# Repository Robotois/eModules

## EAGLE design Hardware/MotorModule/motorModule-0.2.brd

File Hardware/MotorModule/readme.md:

# Motor Module

The motor module is powered by the MCU [ATMEGA328](http://www.atmel.com/devices/atmega328.aspx), as you can see this is the same MCU used in the Arduino [UNO](https://www.arduino.cc/en/Main/ArduinoBoardUno). The firmware of this MCU was coded to control two motors using PWM signals. Until the last version of this module, the firmware for the ATMEGA328 is coded in C language (AVR).

This module has the following features:

* An open firmware for the ATMEGA328, this means that you can modify the code or even use Arduino sketches. The module has an SPI interface for programming the MCU.

* This module is ready for controlling motors without feedback, this means that we can control the direction of rotation, and control the speed by PWM signals.

* Also, the motor module has the necessary components to implement speed and direction control using quadrature encoder sensors. The quadrature sensors provide a reliable feedback for controlling the speed of the motor and therefore we can control the speed of the wheels of a robot.

* There are two lines of the RJ25 connector that provide the voltage for the motors, the advantage of this configuration is that we will have a better current flow trough the cables. The voltage to power up the motors is taken directly from the batteries. The typical voltages of a LiPo battery are: 7.4V for a two cell in series (2S) configuration and 11.1V for 3 cells in series (3S).

* The driver for the motors consists of the IC [TB6612FNG](https://www.sparkfun.com/products/9457), this IC was chosen because it is basically a Mosfet H-bridge and it is efficient enough for small robot applications.

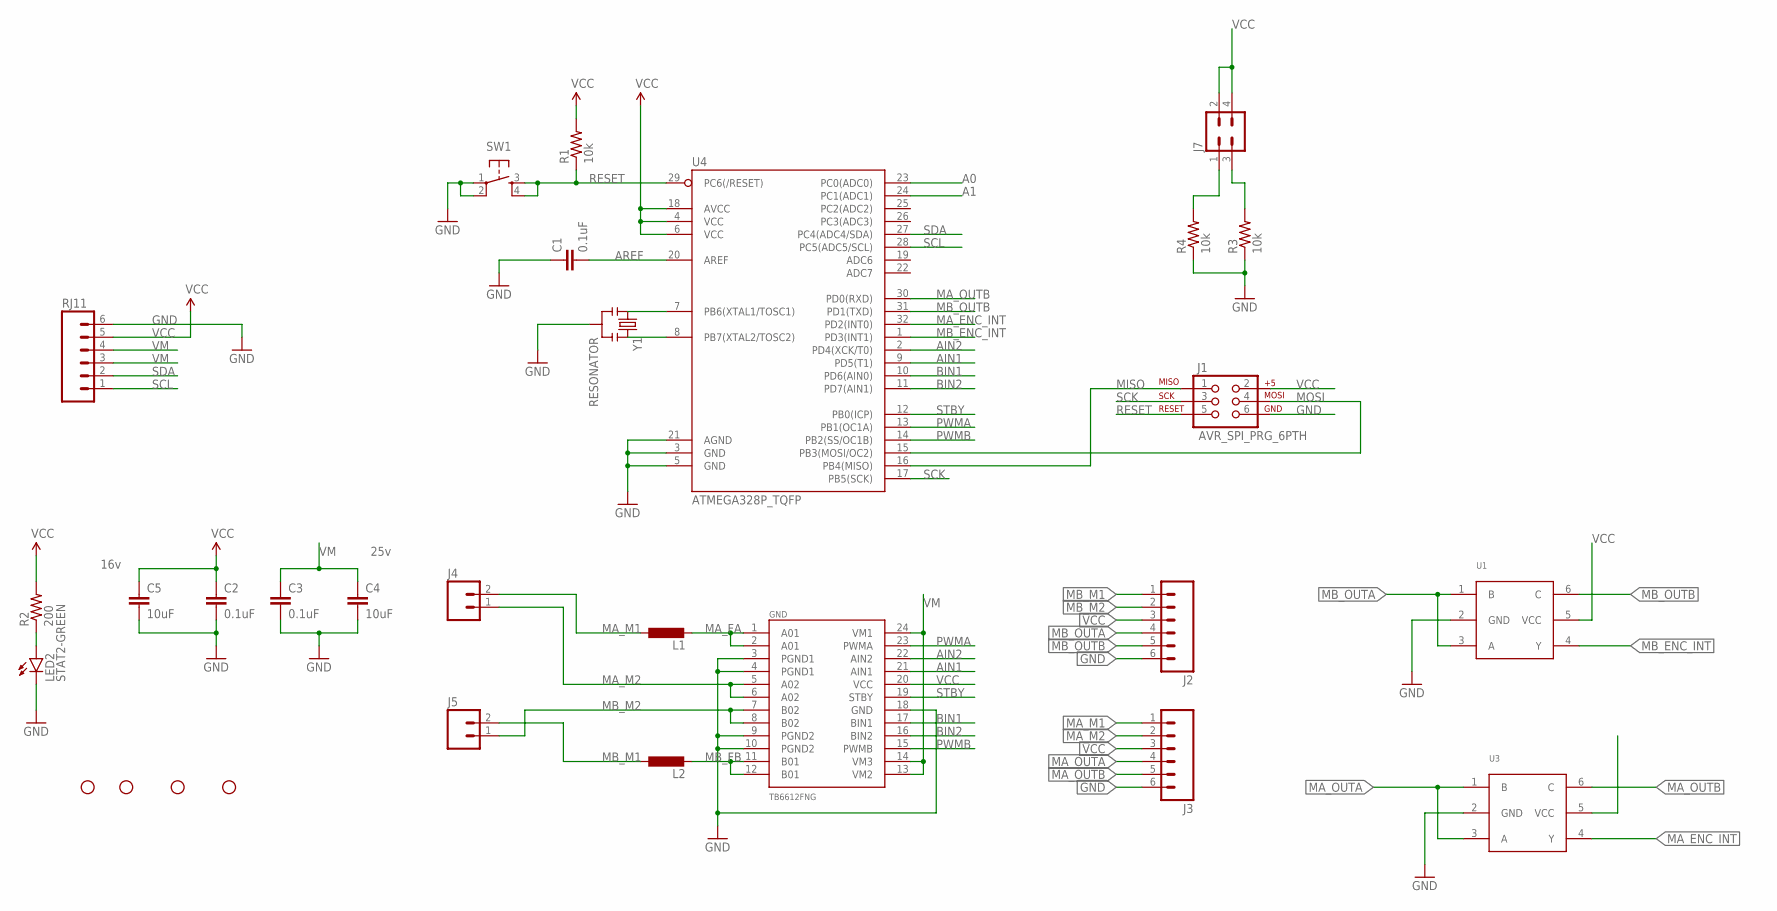
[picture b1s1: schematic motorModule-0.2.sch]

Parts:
C1, C2, C3: 0.1uF; 0603-CAP
C4, C5: 10uF; 0805
GND: TB6612FNG; SSOP24
H1, H2, H3, H4: STAND-OFFPLATED; STAND-OFF-PLATED
J1: AVR_SPI_PRG_6PTH; 2X3
J2, J3: M06JST-PH-6TH; JST-PH-6-TH
J4, J5: M02JST-PTH-VERT; JST-2-PTH-VERT
J7: M02X2; 2X2
L1, L2: L-EUL1812; L1812
LED2: STAT2-GREEN; LED-0603
R1, R3, R4: 10k; 0603-RES
R2: 200; 0603-RES
RJ11: M06RJ11; RJ11-6P6C
SW1: SWITCH_SPST_4_PINKMR2; TACTILE_SWITCH_SMD-3
U1, U3: 74LVC1G58; SOT363
U4: ATMEGA328P_TQFP; TQFP32-08
Y1: RESONATOR; RESONATOR-MURATA

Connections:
A0: J7.3, R3.2, U4.23 (PC0(ADC0))
A1: J7.1, R4.2, U4.24 (PC1(ADC1))
AIN1: GND.21 (AIN1), U4.9 (PD5(T1))
AIN2: GND.22 (AIN2), U4.2 (PD4(XCK/T0))
AREF: C1.2, U4.20 (AREF)
BIN1: GND.17 (BIN1), U4.10 (PD6(AIN0))
BIN2: GND.16 (BIN2), U4.11 (PD7(AIN1))
GND: C1.1, C2.2, C3.2, C4.2, C5.2, GND.3 (PGND1), GND.4 (PGND1), GND.9 (PGND2), GND.10 (PGND2), GND.18 (GND), J1.6, J2.6, J3.6, LED2.C, R3.1, R4.1, RJ11.6, SW1.1, SW1.2, U1.2 (GND), U3.2 (GND), U4.3 (GND), U4.5 (GND), U4.21 (AGND), Y1.2
MA_ENC_INT: U3.4 (Y), U4.32 (PD2(INT0))
MA_FA: GND.1 (A01), GND.2 (A01), L1.2
MA_M1: J3.1, J4.2, L1.1
MA_M2: GND.5 (A02), GND.6 (A02), J3.2, J4.1
MA_OUTA: J3.4, U3.1 (B), U3.3 (A)
MA_OUTB: J3.5, U3.6 (C), U4.30 (PD0(RXD))
MB_ENC_INT: U1.4 (Y), U4.1 (PD3(INT1))
MB_FB: GND.11 (B01), GND.12 (B01), L2.2
MB_M1: J2.1, J5.2, L2.1
MB_M2: GND.7 (B02), GND.8 (B02), J2.2, J5.1
MB_OUTA: J2.4, U1.1 (B), U1.3 (A)
MB_OUTB: J2.5, U1.6 (C), U4.31 (PD1(TXD))
MISO: J1.1, U4.16 (PB4(MISO))
MOSI: J1.4, U4.15 (PB3(MOSI/OC2))
unnamed: U4.7 (PB6(XTAL1/TOSC1)), Y1.1
unnamed: U4.8 (PB7(XTAL2/TOSC2)), Y1.3
unnamed: LED2.A, R2.1
PWMA: GND.23 (PWMA), U4.13 (PB1(OC1A))
PWMB: GND.15 (PWMB), U4.14 (PB2(SS/OC1B))
RESET: J1.5, R1.1, SW1.3, SW1.4, U4.29 (PC6(/RESET))
SCK: J1.3, U4.17 (PB5(SCK))
SCL: RJ11.1, U4.28 (PC5(ADC5/SCL))
SDA: RJ11.2, U4.27 (PC4(ADC4/SDA))
STBY: GND.19 (STBY), U4.12 (PB0(ICP))
VCC: C2.1, C5.1, GND.20 (VCC), J1.2, J2.3, J3.3, J7.2, J7.4, R1.2, R2.2, RJ11.5, U1.5 (VCC), U3.5 (VCC), U4.4 (VCC), U4.6 (VCC), U4.18 (AVCC)
VM: C3.1, C4.1, GND.13 (VM2), GND.14 (VM3), GND.24 (VM1), RJ11.3, RJ11.4

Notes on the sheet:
16v
25v

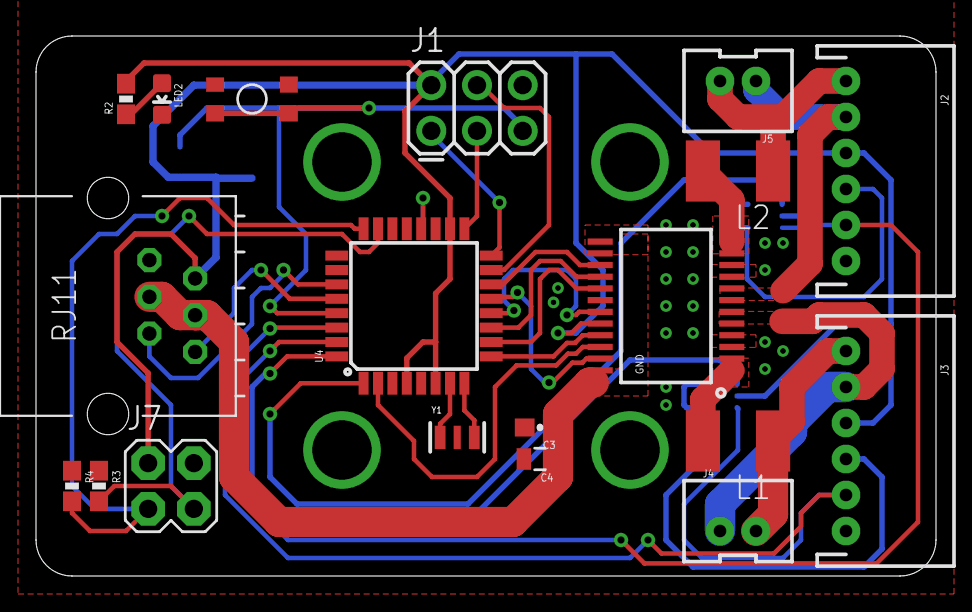
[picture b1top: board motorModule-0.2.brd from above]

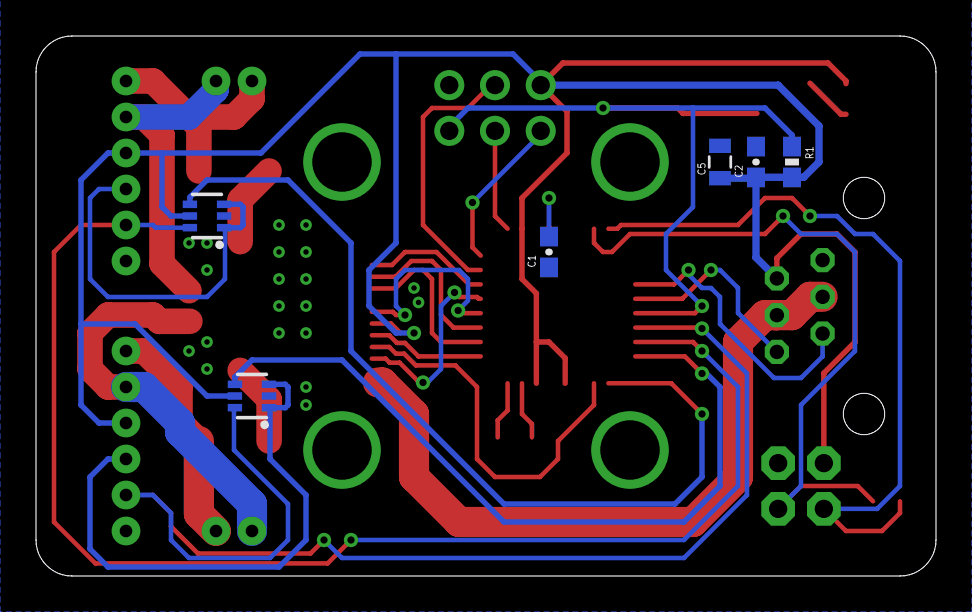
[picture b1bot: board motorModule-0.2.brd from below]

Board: 2 copper layers, 50.0 x 30.0 mm, 29 parts (6 on the bottom side), 34 nets.

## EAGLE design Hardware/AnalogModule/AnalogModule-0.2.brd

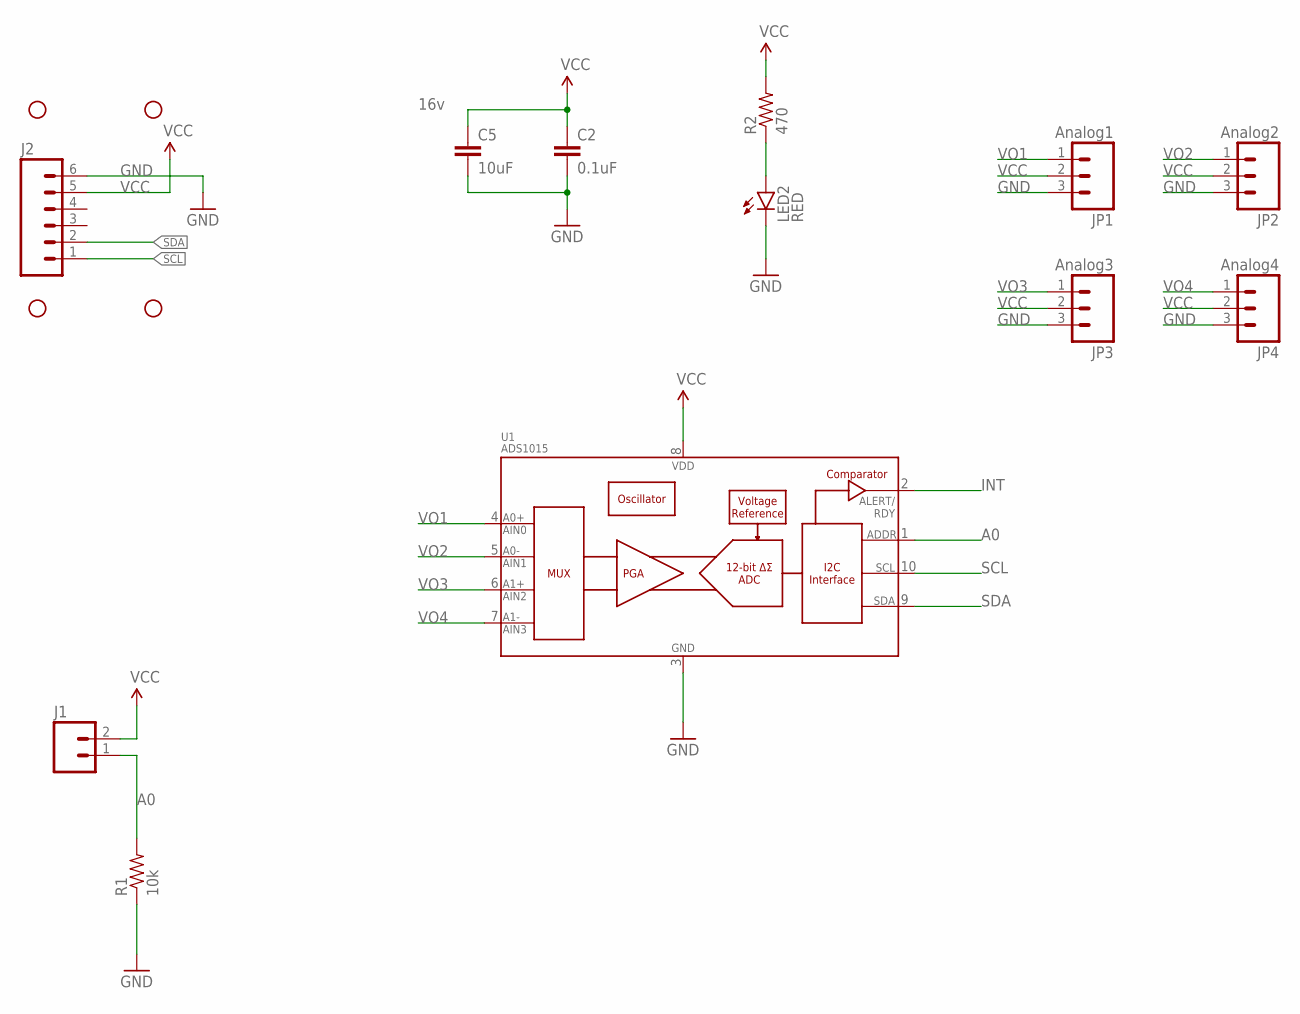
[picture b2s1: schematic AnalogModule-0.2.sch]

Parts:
C2: 0.1uF; 0603-CAP
C5: 10uF; 0805
H1, H2, H3, H4: STAND-OFFPLATED; STAND-OFF-PLATED
J1: M02PTH; 1X02
J2: M06RJ11; RJ11-6P6C
JP1: Analog1; JST-3-PTH-VERT
JP2: Analog2; JST-3-PTH-VERT
JP3: Analog3; JST-3-PTH-VERT
JP4: Analog4; JST-3-PTH-VERT
LED2: RED; LED-0603
R1: 10k; 0603-RES
R2: 470; 0603-RES
U1: ADS1015; MSOP10

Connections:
A0: J1.1, R1.2, U1.1 (ADDR)
GND: C2.2, C5.2, J2.6, JP1.3, JP2.3, JP3.3, JP4.3, LED2.C, R1.1, U1.3 (VSS)
INT: U1.2 (ALERT/RDY)
unnamed: LED2.A, R2.1
SCL: J2.1, U1.10 (SCL)
SDA: J2.2, U1.9 (SDA)
VCC: C2.1, C5.1, J1.2, J2.5, JP1.2, JP2.2, JP3.2, JP4.2, R2.2, U1.8 (VDD)
VO1: JP1.1, U1.4 (AIN0)
VO2: JP2.1, U1.5 (AIN1)
VO3: JP3.1, U1.6 (AIN2)
VO4: JP4.1, U1.7 (AIN3)

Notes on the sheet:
16v

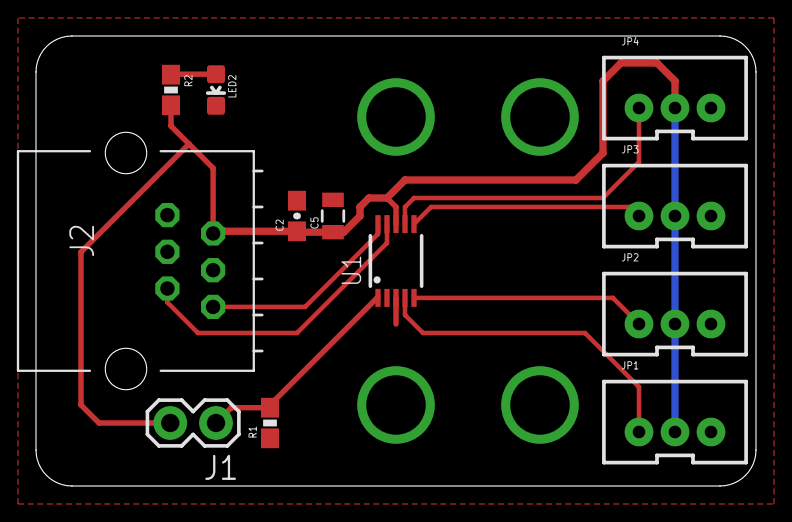
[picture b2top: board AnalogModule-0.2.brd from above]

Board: 2 copper layers, 40.0 x 25.0 mm, 16 parts (0 on the bottom side), 10 nets.

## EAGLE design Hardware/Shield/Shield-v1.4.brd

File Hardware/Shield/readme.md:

# Shield Module
This folder contains the [Eagle](https://cadsoft.io/) files for the Shield Module. It is provided a pdf file of the [schematics](Shield-0.6.pdf), that way it is easier to get an idea of what it contains.

The design of the Shield can be resumed in the following features:

* A reverse polarity protection circuit. The name of this circuit is very intuitive, it protects the Shield and the whole system (Raspberry PI and modules) from negative voltage. This problem happens if we connect the batteries the wrong way.  There is actually a lot of information about this circuit, I would recommend this [video](https://www.youtube.com/watch?v=IrB-FPcv1Dc).

* The load switch, which allows us to manually turn on and off the voltage from the batteries.
Since the Raspberry PI automatically starts when the power supply is active, we want to control when to turn it on, and also we want to disconnect the power supply from the PI (and the whole system) when we are done with our projects. With this load switch we can cut-off the power supply without having to disconnect the battery at all.

* A Buck converter, this is a DC-DC converter, which steps down the voltage from the batteries, since the voltage allowed is in the range of 6V to 12V. The configuration for this converter is a switching regulator, and it will provide the 5V voltage required for the Raspberry PI and the modules.

* Level shifters for I2C communication, these modules protects the I2C port of the PI from an incoming signal greater than 3.3V. We use this shifters because some of the modules we designed operates at 5V.

* In general all the modules connects to the Shield using a RJ25 connector, which consists of 6 lines, two for power supply, two for I2C communication (SDA and SCL) and two digital inputs/outputs. These connectors are generic, which means that we can connect any module to any connector.

* The RJ25 connectors for Motors/Servos modules are different because we use two lines to power the motors/servos. The power supply for the motors/servos is taken directly from the batteries (except for the basic servo module, it takes the power supply from the 5V of the Shield).

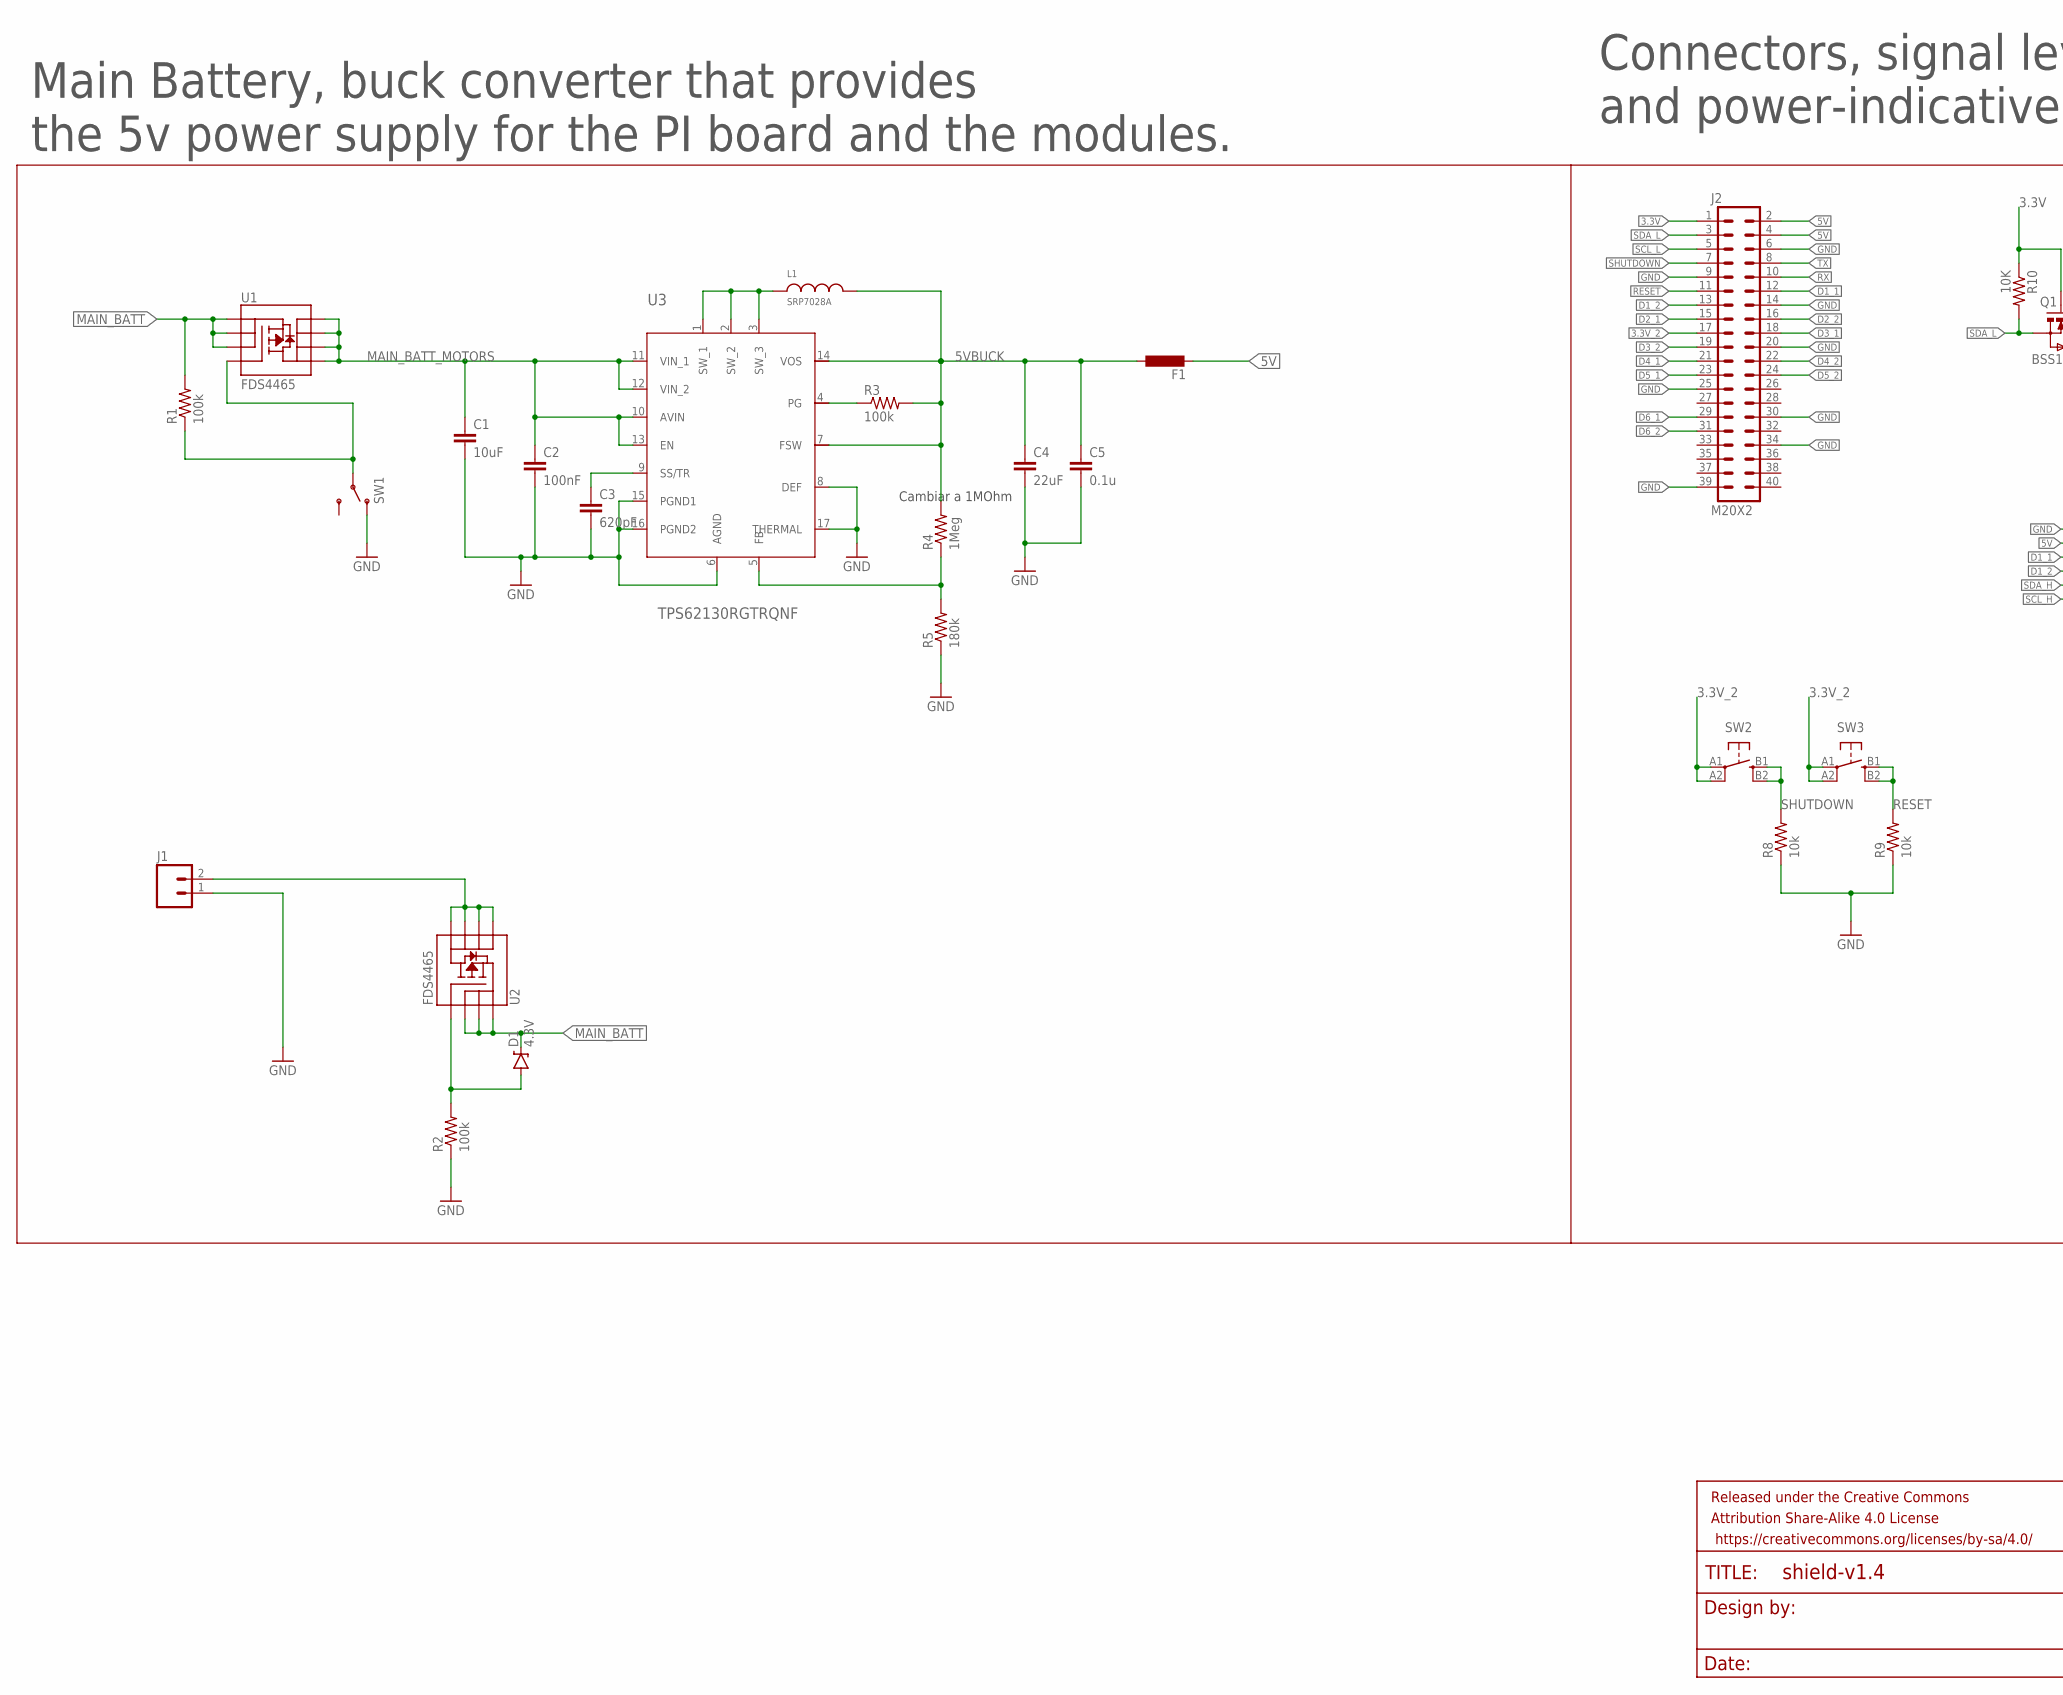
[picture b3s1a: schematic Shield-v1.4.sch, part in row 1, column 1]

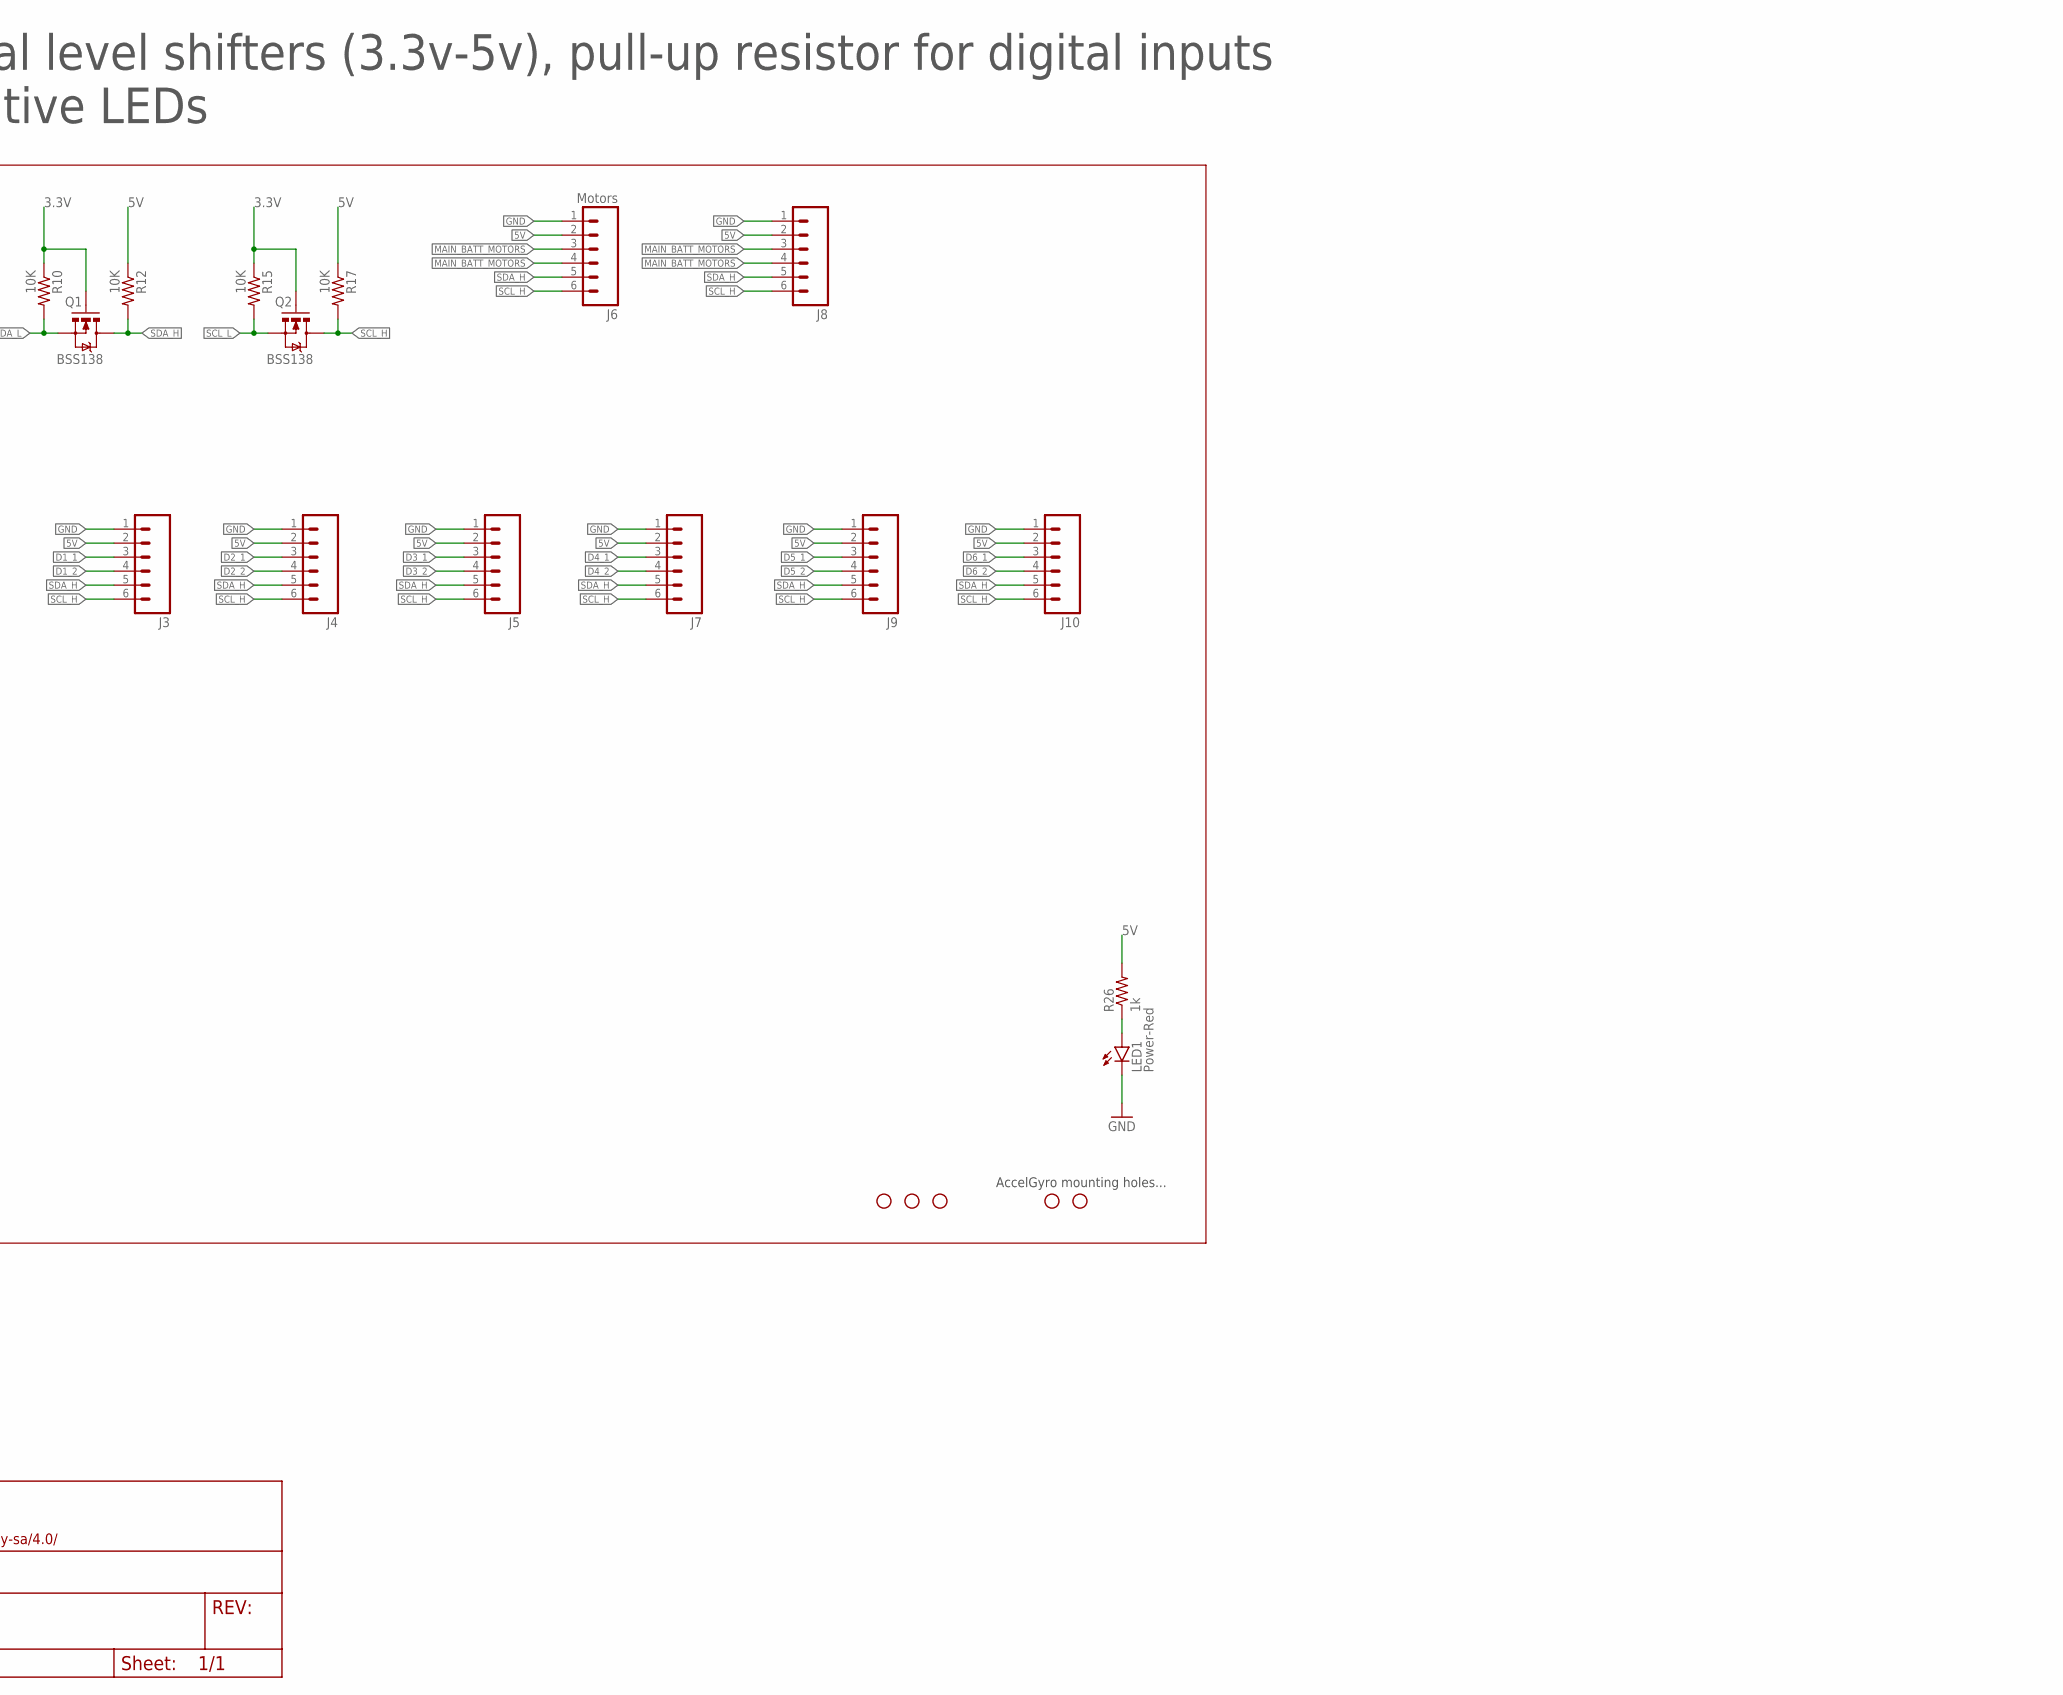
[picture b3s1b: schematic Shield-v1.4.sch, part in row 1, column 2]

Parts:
C1: 10uF; 0603-CAP
C2: 100nF; 0603-CAP
C3: 620pF; 0603-CAP
C4: 22uF; 0805
C5: 0.1u; 0603-CAP
D1: 4.3V; SOD-323
F1: L-EUL1812; L1812
FRAME1: FRAME-LETTERNO_PACKAGE; DUMMY
H1, H2: STAND-OFFPLATED; STAND-OFF-PLATED
H3: STAND-OFFNORMAL; STAND-OFF
H4, H5: STAND-OFF
J1: M02PTH-XH; JST-2-PTH-XH
J2: M20X2; 2X20
J3, J4, J5, J7, J8: M06RJ11; RJ11-6P6C
J6: Motors; RJ11-6P6C
J9, J10: M06RJ11-SMD; RJ11-6P6C-SMD
L1: SRP7028A
LED1: Power-Red; LED-0603
Q1, Q2: BSS138; SOT23-3
R1, R2, R3: 100k; 0603-RES
R4: 1Meg; 0603-RES
R5: 180k; 0603-RES
R8, R9: 10k; 0603-RES
R10, R12, R15, R17: 10K; 0603-RES
R26: 1k; 0603-RES
SW1: SWITCH-SPDT-SPDT-TH; SW-SPDT-TH
SW2, SW3: SWITCH_SPST_4_PINTALL; TACTILE_SWITCH_TALL
U1, U2: FDS4465; SO08
U3: TPS62130RGTRQNF; QFN-N16

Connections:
3.3V: J2.1, Q1.1 (G), Q2.1 (G), R10.1, R15.1
3.3V_2: J2.17, SW2.A1 (1), SW2.A2 (2), SW3.A1 (1), SW3.A2 (2)
5V: F1.2, J2.2, J2.4, J3.2, J4.2, J5.2, J6.2, J7.2, J8.2, J9.2, J10.2, R12.1, R17.1, R26.2
5VBUCK: C4.1, C5.1, F1.1, L1.P$2 (2), R3.2, R4.2, U3.7 (FSW), U3.14 (VOS)
D1_1: J2.12, J3.3
D1_2: J2.13, J3.4
D2_1: J2.15, J4.3
D2_2: J2.16, J4.4
D3_1: J2.18, J5.3
D3_2: J2.19, J5.4
D4_1: J2.21, J7.3
D4_2: J2.22, J7.4
D5_1: J2.23, J9.3
D5_2: J2.24, J9.4
D6_1: J2.29, J10.3
D6_2: J2.31, J10.4
GND: C1.2, C2.2, C3.2, C4.2, C5.2, J1.1, J2.6, J2.9, J2.14, J2.20, J2.25, J2.30, J2.34, J2.39, J3.1, J4.1, J5.1, J6.1, J7.1, J8.1, J9.1, J10.1, LED1.C, R2.1, R5.1, R8.1, R9.1, SW1.P$3 (O), U3.6 (AGND), U3.8 (DEF), U3.15 (PGND1), U3.16 (PGND2), U3.17 (THERMAL)
MAIN_BATT: D1.C, R1.2, U1.1 (S), U1.2 (S), U1.3 (S), U2.1 (S), U2.2 (S), U2.3 (S)
MAIN_BATT_MOTORS: C1.1, C2.1, J6.3, J6.4, J8.3, J8.4, U1.5 (D), U1.6 (D), U1.7 (D), U1.8 (D), U3.10 (AVIN), U3.11 (VIN_1), U3.12 (VIN_2), U3.13 (EN)
MAIN_VBATT: J1.2, U2.5 (D), U2.6 (D), U2.7 (D), U2.8 (D)
unnamed: C3.1, U3.9 (SS/TR)
unnamed: L1.P$1 (1), U3.1 (SW_1), U3.2 (SW_2), U3.3 (SW_3)
unnamed: R3.1, U3.4 (PG)
unnamed: R4.1, R5.2, U3.5 (FB)
unnamed: LED1.A, R26.1
unnamed: D1.A, R2.2, U2.4 (G)
unnamed: R1.1, SW1.P$2, U1.4 (G)
RESET: J2.11, R9.2, SW3.B1 (3), SW3.B2 (4)
RX: J2.10
SCL_H: J3.6, J4.6, J5.6, J6.6, J7.6, J8.6, J9.6, J10.6, Q2.3 (D), R17.2
SCL_L: J2.5, Q2.2 (S), R15.2
SDA_H: J3.5, J4.5, J5.5, J6.5, J7.5, J8.5, J9.5, J10.5, Q1.3 (D), R12.2
SDA_L: J2.3, Q1.2 (S), R10.2
SHUTDOWN: J2.7, R8.2, SW2.B1 (3), SW2.B2 (4)
TX: J2.8

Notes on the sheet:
AccelGyro mounting holes...
Main Battery, buck converter that provides the 5v power supply for the PI board and the modules.
Connectors, signal level shifters (3.3v-5v), pull-up resistor for digital inputs and power-indicative LEDs
Cambiar a 1MOhm

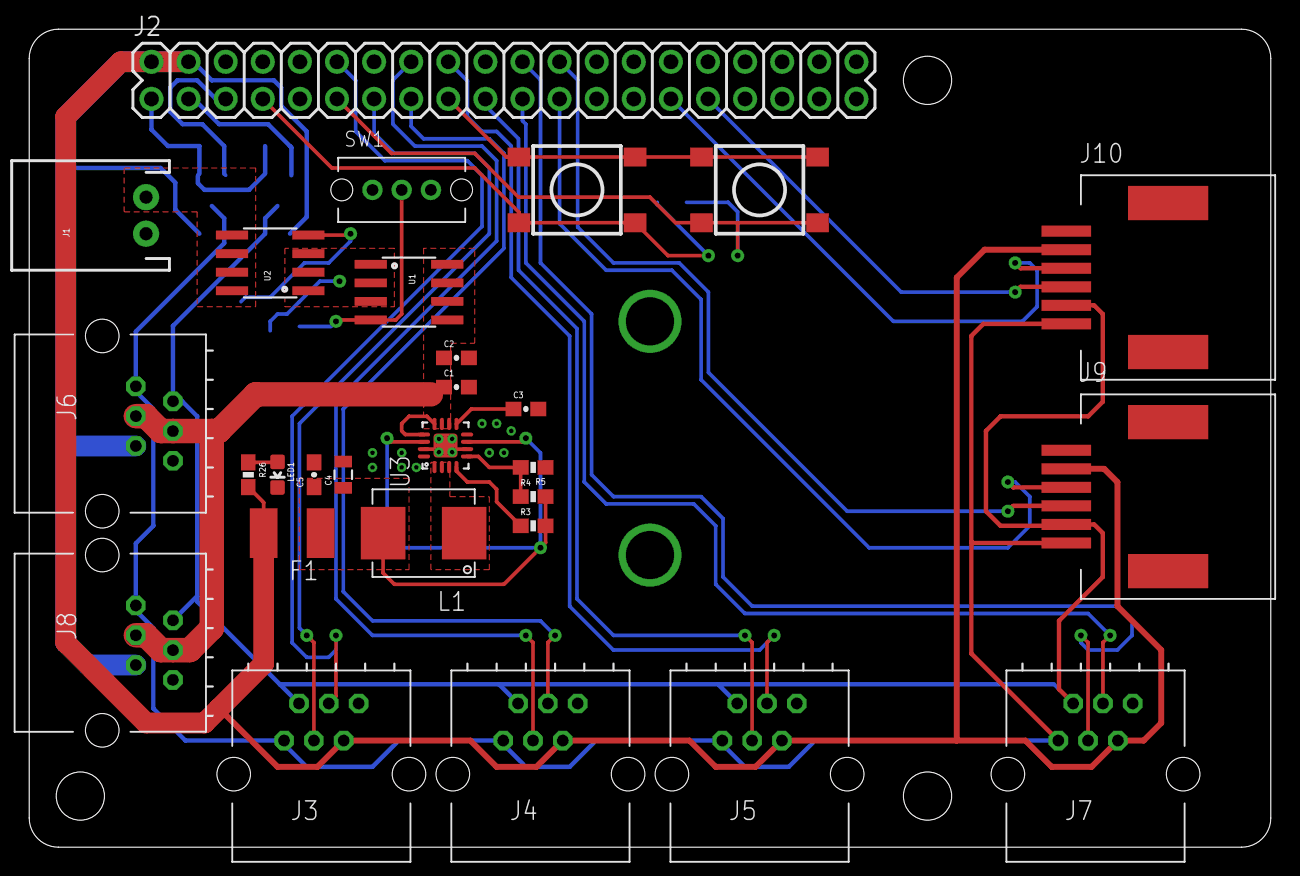
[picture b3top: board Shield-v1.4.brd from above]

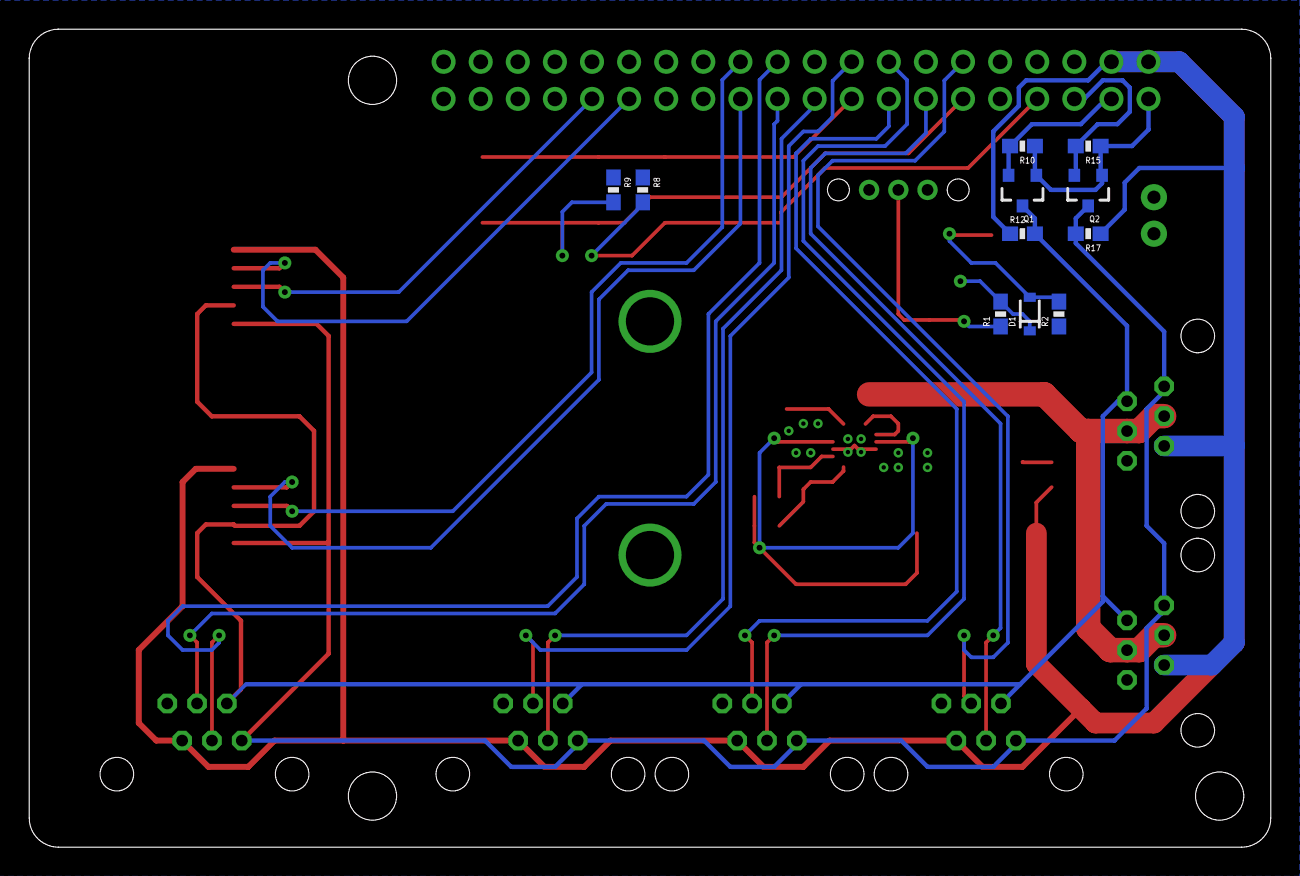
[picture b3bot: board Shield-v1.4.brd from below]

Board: 2 copper layers, 85.0 x 56.0 mm, 45 parts (11 on the bottom side), 33 nets.

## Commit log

2016-02-18 Actualizacion del control PID
2016-02-20 Pruebas con el modulo AccelGyro
2016-05-21 In this commit we are pushing raw code used for testing modules, in future commits we'll provide a better organized code in a modular fashion.
2016-06-01 New Libraries and Modules implemented in c++.
2016-06-01 Added new modules...
2016-06-02 Motor Module class updates...
2016-06-09 Added the Node Library folder and some initial tests
2016-06-09 Node Libraries for the analog modules...
2016-06-09 Added Ultrasonic and LCD modules to the Node library
2016-06-10 New Node libraries, RGB LEDs, Line Sensors and Servos...
2016-06-20 Major updates in the NodeLibrary and the base C++ code...
2016-06-21 Exit handler for LEDs and Buttons
2016-06-21 Button lib fixes...
2016-06-21 Updates in the Node library...
2016-08-03 Shield Hardware
    Added the schematics and board layout for the Shield Module
2016-08-04 Shield Updates
2016-08-04 Hardware Docs
2016-09-02 Organizing Code
2016-12-01 Fixes
2016-12-02 Events added to Node libraries
2017-01-05 Added initial led test
2017-01-05 Added new methods to led implementation
2017-01-05 fixed led status
2017-01-05 Added blink proc to led example
2017-01-05 Added light implementation
2017-01-05 updated light port
2017-01-05 changed port to number 1
2017-01-05 Added support for getValue method for analog sensors
2017-01-05 Added support for getValue method for temperature module
2017-01-06 Added change getValue implementation rotatory
2017-01-06 Added when support for light sensor
2017-01-06 code higiene
2017-01-06 Added when implementation for the rest of the moduels
2017-01-07 Added log to tell when is fired when
2017-01-07 remove log for when
2017-01-07 due normal comparison between strings and integers
2017-01-07 fixed issue temp module
2017-01-09 Code higiene lcd module
2017-01-10 Added support for blinking lcd
2017-01-10 Fixed issues with setText method
2017-01-10 Code higiene and lcd blink implementation
2017-01-10 Added suppor for blinking method for 2 secs
2017-01-10 fixed typo
2017-01-10 udpated sensing fecuency to 400 mls
2017-01-10 set scaled value to rotatory
2017-01-18 Fixed typo issue with button module
2017-01-18 Added correct when implementation to push button
2017-01-18 enhanced push button implementation
2017-01-18 refactor when implementation push buttton
2017-01-19 Added turnOn method
2017-01-19 hex to RBG method
2017-01-19 added support for leds numbers
2017-01-20 Added blink suppor to lcd
2017-01-20 Netbeans config
2017-01-20 debug code
2017-01-20 hextorgb implementation
2017-01-20 Added support for converting correctly the rgb value
2017-01-20 implemented rgb function
2017-01-20 rgb refactor
2017-01-20 implemented blinking for led rgb
2017-01-26 Node Library Updates
2017-01-27 logs
2017-01-28 Bugs
2017-01-28 merged from master
2017-01-28 fix typo
2017-01-28 added logging of sacaled values for testing
2017-01-30 Added support to clean the interval for temperature and light sensor
2017-01-30 Added clear interval function for rotatory and ultrasonic sensor
2017-01-30 pruebas
2017-02-16 Added better logs
2017-02-16 Added support for logs button
2017-02-25 Reading multiple sensors from Analog Module
2017-02-25 gave format to outputs
2017-05-15 Several updates
2017-06-17 Importing Robotois Modules as submodules
2017-06-17 Adding Sound Sensor module
2017-07-03 New project organization
2017-08-25 New modules added
2017-09-02 Libraries for Motor and Servo

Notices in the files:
parts and their libraries:
SparkFun-Capacitors: Licensing: Creative Commons ShareAlike 4.0 International - https://creativecommons.org/licenses/by-sa/4.0
SparkFun-Aesthetics: Released under the Creative Commons Attribution Share-Alike 4.0 License
SparkFun-Aesthetics: https://creativecommons.org/licenses/by-sa/4.0
